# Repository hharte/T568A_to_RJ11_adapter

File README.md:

## T568A to RJ11 Adapter

## Introduction

The T568A to RJ11 Adapter is a small board that adapts from a standard 8P8C modular jack with [T568A wiring](https://en.wikipedia.org/wiki/ANSI%2FTIA-568#Wiring) to four [RJ11](https://en.wikipedia.org/wiki/Registered_jack#RJ11,_RJ14,_RJ25_wiring) modular jacks.  **_Note: If you use T568B wiring, RJ11 ports 3 and 4 will be swapped, but otherwise this adapter will work fine._**

## Status

The Issue 1 boards have been fabricated, hand assembled, and tested to work well.

## Bill of Materials

Online [DigiKey BOM](https://www.digikey.com/en/mylists/list/4QF6TJ3CTL).  [Interactive BOM](https://html-preview.github.io/?url=https://github.com/hharte/T568A_to_RJ11_adapter/blob/main/hardware/bom/ibom.html).

<table>
  <tr>
   <td>Quantity
   </td>
   <td>Reference Designator
   </td>
   <td>Value
   </td>
  </tr>
  <tr>
   <td>4
   </td>
   <td>J1, J2, J3, J4
   </td>
   <td>6P6C<sup>[1]</sup>
   </td>
  </tr>
  <tr>
   <td>1
   </td>
   <td>J5
   </td>
   <td>8P8C
   </td>
  </tr>
</table>

<sup>[1]</sup> Note: 6P6C, 6P4C, or 6P2C connectors may be used.

In addition to the electrical parts in the BOM, the following hardware is required when building the supplied 3D enclosure.

<table>
  <tr>
   <td>Quantity
   </td>
   <td>Description
   </td>
   <td>Link
   </td>
  </tr>
  <tr>
   <td>4
   </td>
   <td>M3x6mm Phillips screws
   </td>
   <td><a href="https://www.amazon.com/Uxcell-a15070200ux0064-Stainless-Phillips-Screws/dp/B012TE12CY">Amazon link</a>
   </td>
  </tr>
  <tr>
   <td>2
   </td>
   <td>M3x15 + 6mm standoffs.
   </td>
   <td><a href="https://www.amazon.com/Hxchen-Female-Hexagon-Standoff-Pillars/dp/B07WR5ZD8G">Amazon link</a>
   </td>
  </tr>
</table>

## Enclosure

A 3D-printable enclosure designed with [FreeCAD](https://www.freecad.org/) is provided.  The PCB mounts to the bottom half of the enclosure, secured with three M3x6mm screws, and two M3x15+6mm threaded standoffs.  The top half of the enclosure is attached to the standoff in the middle of the board using one M3x6mm screw.

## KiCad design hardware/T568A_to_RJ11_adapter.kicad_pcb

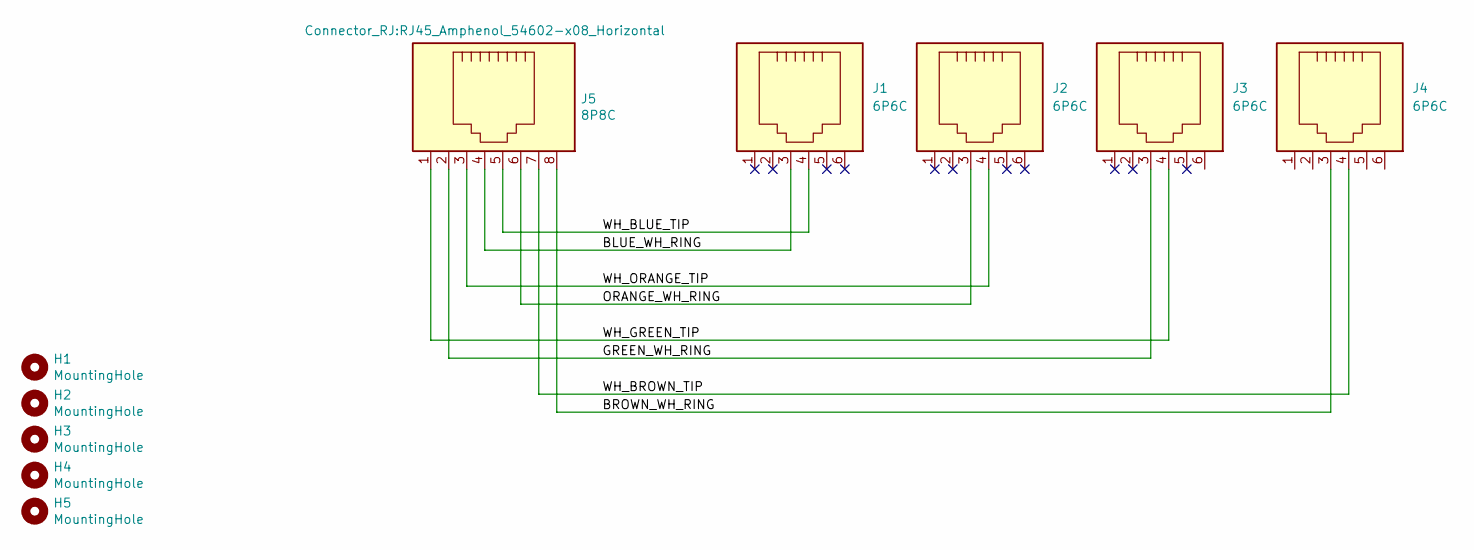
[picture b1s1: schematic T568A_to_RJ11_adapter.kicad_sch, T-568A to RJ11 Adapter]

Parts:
H1, H2, H3, H4, H5: MountingHole; MountingHole_3.2mm_M3_Pad
J1, J2, J3, J4: 6P6C; RJ12_Amphenol_54601-x06_Horizontal
J5: 8P8C; RJ45_Amphenol_54602-x08_Horizontal; MPN 54602-908LF; Digi-Key_PN 609-1046-ND

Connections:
/BLUE_WH_RING: J1.3, J5.4
/BROWN_WH_RING: J4.3, J5.8
/GREEN_WH_RING: J3.3, J5.2
/ORANGE_WH_RING: J2.3, J5.6
/WH_BLUE_TIP: J1.4, J5.5
/WH_BROWN_TIP: J4.4, J5.7
/WH_GREEN_TIP: J3.4, J5.1
/WH_ORANGE_TIP: J2.4, J5.3

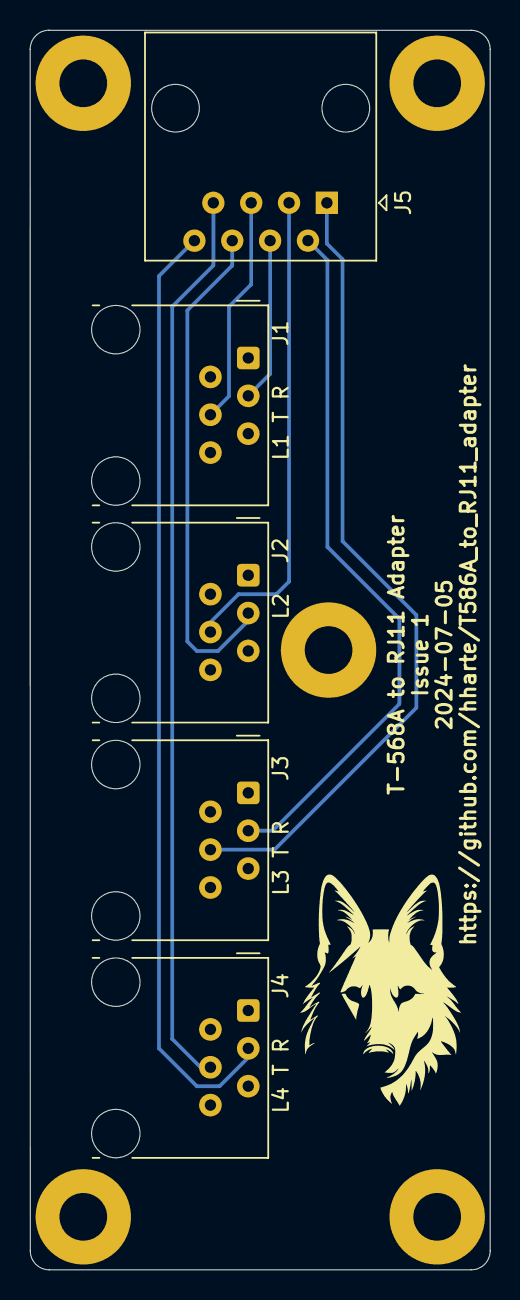
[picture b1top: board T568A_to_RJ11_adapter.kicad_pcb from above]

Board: 2 copper layers, 30.9 x 83.2 mm, 11 parts (0 on the bottom side), 8 nets.

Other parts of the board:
Deena: LOGO; Deena

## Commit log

2024-07-06 Issue 1 PCB ready for fabrication.
2024-07-15 Add 3D-printable enclosure.
2024-07-20 Update BOM and add photo of finished project.
